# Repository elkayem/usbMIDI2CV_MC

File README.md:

# usbMIDI2CV_MC

This repository contains the code and schematics for a three-channel USB-MIDI to CV converter.  STL files are also included for a 3D printed case.  This project has the following features:
* Three channel Note CV output (88 keys, 1V/octave, MIDI channels 1-3) using a 12-bit DAC
* Configurable note priority for each channel (Top Note, Bottom Note, or Last Note Priority)
* Note scale factor calibration configurable in software
* 5V Gate/Trigger outputs, where each channel can be independently configured to either output a gate (output high for entire length of time that note is on) or trigger (20 msec pulse each time a new note is initiated)
* Velocity CV output (0 to 4V) for each channel
* Pitch Bend CV output (0.5 +/- 0.5V), which can be configured for channel 1, 2, or 3
* Control Change CV output (0 to 4V), which can be configured for channel 1, 2, or 3
* OLED user interface, used for setting parameters and saving to EEPROM

This module is the perfect interface between your computer or iPad and an analog synthesizer.  It can independently drive up to three oscillators with 1V/octave CV inputs.  (Connection to an iPad requires the USB camera adapter but is well worth it given the wide variety of great MIDI sequencer apps.)  

Note priority can be independengly set for each channel, with the following options:
* **Top Note (aka Highest Note):** When multiple notes are sounded simultaneously, the highest note being held will be sounded.  When the highest note is released, the next highest note will be played, and so on.
* **Bottom Note (aka Lowest Note):** Analagous to top note, except the lowest note being held will be sounded.  
* **Last Note:** The most recent note played will be sounded.  When that note is released, the next most recent note still being held will be sounded.  

The settings screen shows the current settings used.  Note priority is listed as sequence of three letters showing the setting for each of the three channels, where T = Top Note, B = Bottom Note, and L = Last Note.  Similarly, Gate/Trigger is listed as a sequence of three letters where G = Gate and T = Trigger.  Pitch Bend and CC settings show which MIDI channel will be used for the analog output.  Note scale factor can also be calibrated by +/-10%.  All of these settings can be set through the OLED interface using the encoder knob.

## Parts List
* Teensy 2.0
* LM7805 5V Voltage Regulator
* 128x64 OLED graphic display, with I2C interface 
* Pushbutton Rotary encoder with knob (should have 5 pins)
* 4x MCP4822 12-bit DACs (8 pin DIP)
* 2x LM324N Quad Op Amp (14 pin DIP)
* 7x 0.1 uF ceramic capacitors
* 0.33 uF capacitor
* 3x 3K resistors (1% metal film)
* 3x 4.7K resistors (1% metal film)
* 3x 10K resistors (1% metal film)
* 3x 2K resistors
* 4x 8 pin DIP IC sockets
* 2x 14 pin DIP IC sockets
* 2x 12-pin female headers
* 8x banana jacks
* 3x 1/4" mono phone jacks
* (Optional) 2-pin 5.08mm pitch screw terminal, for power input 
* Barrel power jack (e.g., 2.1 x 5.5 mm)
* 9 - 12V DC power supply with barrel connector (e.g., 2.1 x 5.5 mm)
* PCB (Gerber files included) or strip board
* 6x 10mm M3 bolts and nuts (4 for panel, 2 for USB port)
* 4x M2 bolts and nuts for mounting the OLED screen
* Panel mount USB 2.0 USB Mini B Female to USB Mini B Male, 1 ft cable (see picture below)

## Instructions
Electronic components can be soldered to a strip board or (more conveniently) to the PCB design I have included in this repository.  I recommend using IC sockets to mount the ICs and female headers to mount the Teensy.  The PCB can be manufactured by a PCB supplier.  The least expensive way to do this is to upload the gerber files (included as a .zip file) to one of several Chinese manufacturers such as SchenZhen2U, EasyEDA, or Seeed Studio.  pcbshopper.com allows a comparison between vendors.  Typical prices are $1-$3/board, with a minimum of 5 boards.  Recommended default settings are Layers: 2; PCB Thickness: 1.6mm; Surface Finish: HASL; Copper Weight: 1.  (Alternatively, contact me since I may still have a few extras I could send out for $5 + shipping.)

**Important!** Before connecting the Teensy 2.0 to an external power supply, the 5V pads must be cut on the bottom side of the board.  See https://www.pjrc.com/teensy/external_power.html for details.

The 3D printer STL files are located in the 3D Printer Files folder. I've also included the Sketchup file, in case modifications are needed.  (Download Sketchup Make, it's free!) The panel includes raised text, and so must be printed with two colors. Most slicers include a "pause at height" plugin, which will move the hot end out of the way and allow you to switch filaments. The panels are 3mm thick, and the letters are 0.45mm thick. I printed with 0.15mm layer thickness, allowing the letters to be printed in three layers. Add the command to pause after you finish printing the 3mm layer, so you can change the filament color. (One tip: If you find that your printer is disabling the stepper motors after pausing, you may need to insert M84 S0 at the start of the G-Code. I did.)  

The 3D printed panel must be printed with supports for the OLED screen mount. There is a recessed area on the back side of the panel that fits the screen mounting shape. I recommend picking up the screen by DIYMall, as the hole pattern was designed for that screen. Others may fit as well. Supports are not required for the case.

I have included 1/4" jacks for the CV note outputs to ensure that the analog synthesizer shares a common ground with the MIDI2CV component.  Ground is carried over the sleeve.  The sleeve pins on the phone jacks need to be tied together, and then tied to a ground location on the PCB.  I did not provide a dedicated ground location on the PCB for this connection, but any location on the PCB will work.  (e.g., directly to the power ground input).  I left the remainder of the outputs as banana jacks assuming at least one of the notes is connected.  If desired, the banana jacks can be replaced with phone jacks.  Be aware that the holes in the 3D printed case may need to be enlarged, and and the case may need to be made taller to accomodate the depth of the additional phone jacks. 

The rotary encoder should have three pins on one side and two on the other.  Connect the three pins to the 3 ENC headers on the board, and the two pins to the 2 BTN pins on the board.  These may be connected using jumper wires and male header pins, or soldered directly to the board.

The OLED attaches to the I2C output on the PCB (marked as 5V, GND, SCL, SDA).  Note the pin order!  This order matches a commonly available OLED from DIYMall, but other OLEDs exist with the power and ground swapped.  Swapping power and ground will destroy the OLED.

The firmware can be uploaded to the Teensy 2.0 using the Teensy loader.  See https://www.pjrc.com/teensy/first_use.html for details.  The hex file is included in this repository.  If modification of the source code is required, then the Arduino software and Teensyduino must also be installed (see https://www.pjrc.com/teensy/td_download.html).  Several libraries are used, which are included as part of the Teensyduino installer.  Be sure to configure the board as Teensy 2.0 (under Tools > Board), and USB Port as MIDI (under Tools > USB Type).

**Important Notes if recompiling firmware:**  
* You must be using Teensyduino 1.45 or later to recompile the software.  Earlier versions used a different internal numbering convention for MIDI message types.  The latest version can be downloaded from https://www.pjrc.com/teensy/td_download.html.  
* If the software isn't compiling, check your library version numbers.  I am currently using Adafruit SSD1306 v1.2.9 and Bounce2 v2.52.2.  The remaining libraries should come preinstalled with the Arduino and Teensyduino installers.

If using 1% metal film resistors, the MIDI2CV is likely to be in tune for the entire 7.25 octave (88 key) range.  The DAC output range is 4.096 V, which is amplified by 7.25/4.096 = 1.7700.  This is accomplished with the combination of 3K, 4.7K, and 10K resistors in the op-amp circuit.  (Note 3.01K is also common, and can be used.)  

If the MIDI2CV output scale factor isn't exactly 1V/octave, the scale factor can be adjusted by +/-10% using the user interface.  Mine was fairly close for all three channels, and required adjustment of only a few tenths of a percent.

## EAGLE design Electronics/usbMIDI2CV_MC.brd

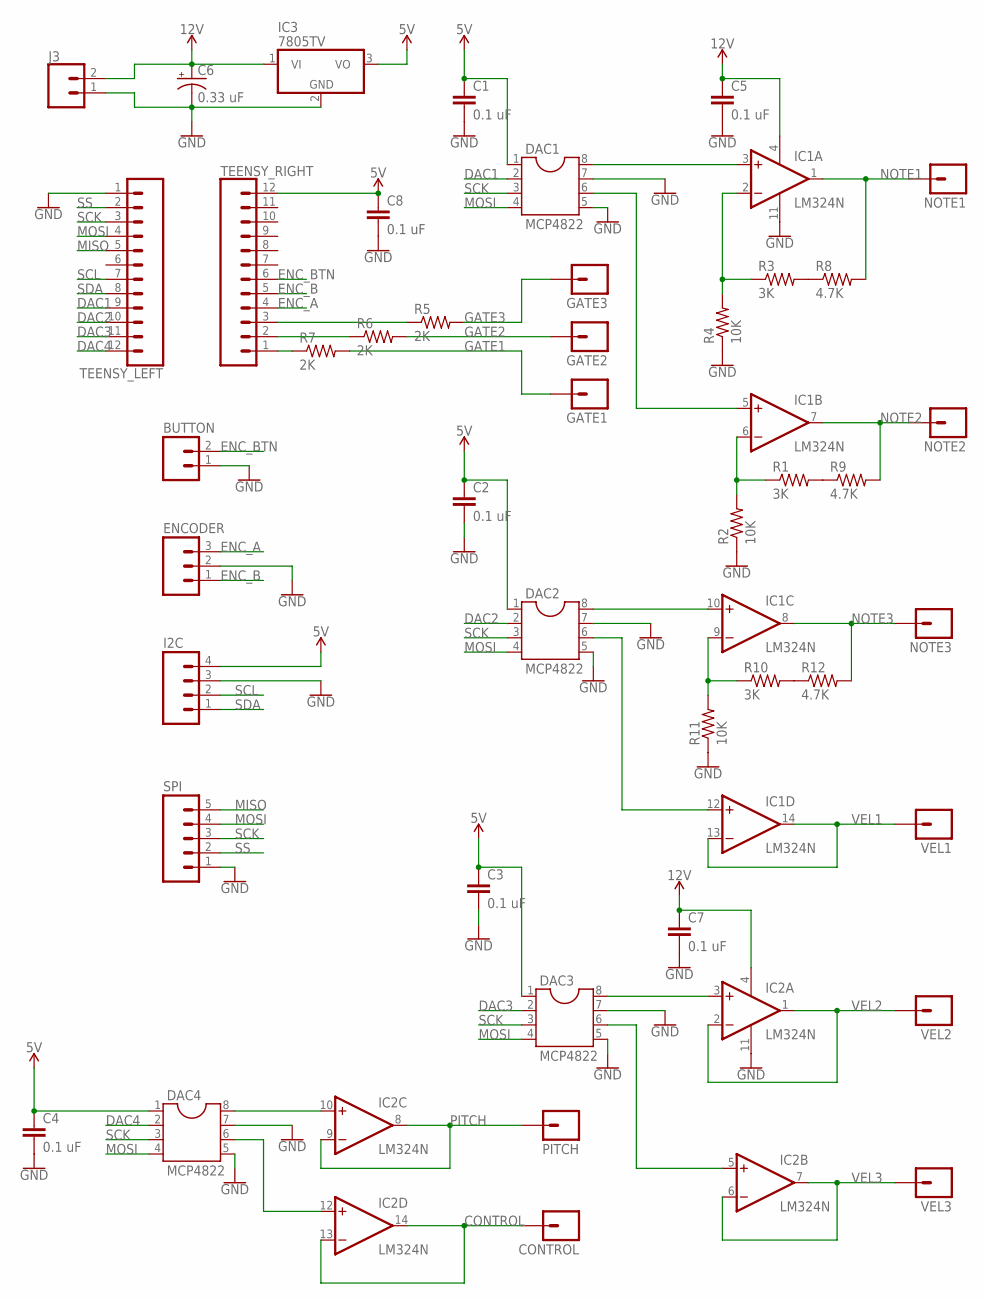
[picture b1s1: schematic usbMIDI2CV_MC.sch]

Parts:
BUTTON: M02LOCK_LONGPADS; 1X02_LOCK_LONGPADS
C1, C2, C3, C4, C5, C7, C8: 0.1 uF; CAP-PTH-SMALL
C6: 0.33 uF; CPOL-RADIAL-100UF-25V
CONTROL: M01PTH_NO_SILK_YES_STOP; 1X01_NO_SILK
DAC1, DAC2, DAC3, DAC4: MCP4822; SOCKET-08
ENCODER: M03LONGPADS; 1X03_LONGPADS
GATE1, GATE2, GATE3: M01PTH_NO_SILK_YES_STOP; 1X01_NO_SILK
I2C: M04LONGPADS; 1X04_LONGPADS
IC1, IC2: LM324N; DIL14
IC3: 7805TV; TO220V
J3: CONN_025MM; SCREWTERMINAL-5MM-2
NOTE1, NOTE2, NOTE3: M01PTH_NO_SILK_YES_STOP; 1X01_NO_SILK
PITCH: M01PTH_NO_SILK_YES_STOP; 1X01_NO_SILK
R1, R3, R10: 3K; 0207/10
R2, R4, R11: 10K; 0207/10
R5, R6, R7: 2K; 0207/10
R8, R9, R12: 4.7K; 0207/10
SPI: M05PTH_LONGPADS; 1X05_LONGPADS
TEENSY_LEFT: CONN_12; 1X12
TEENSY_RIGHT: CONN_12; 1X12
VEL1, VEL2, VEL3: M01PTH_NO_SILK_YES_STOP; 1X01_NO_SILK

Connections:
5V: C1.1, C2.1, C3.1, C4.1, C8.1, DAC1.1, DAC2.1, DAC3.1, DAC4.1, I2C.4, IC3.3 (VO), TEENSY_RIGHT.12
12V: C5.1, C6.1 (+), C7.1, IC1.4 (V+), IC2.4 (V+), IC3.1 (VI), J3.2
CONTROL: CONTROL.1, IC2.13 (-IN), IC2.14 (OUT)
DAC1: DAC1.2, TEENSY_LEFT.9
DAC2: DAC2.2, TEENSY_LEFT.10
DAC3: DAC3.2, TEENSY_LEFT.11
DAC4: DAC4.2, TEENSY_LEFT.12
ENC_A: ENCODER.3, TEENSY_RIGHT.4
ENC_B: ENCODER.1, TEENSY_RIGHT.5
ENC_BTN: BUTTON.2, TEENSY_RIGHT.6
GATE1: GATE1.1, R7.2
GATE2: GATE2.1, R6.2
GATE3: GATE3.1, R5.2
GND: BUTTON.1, C1.2, C2.2, C3.2, C4.2, C5.2, C6.2 (-), C7.2, C8.2, DAC1.5, DAC1.7, DAC2.5, DAC2.7, DAC3.5, DAC3.7, DAC4.5, DAC4.7, ENCODER.2, I2C.3, IC1.11 (V-), IC2.11 (V-), IC3.2 (GND), J3.1, R2.1, R4.1, R11.1, SPI.1, TEENSY_LEFT.1
MISO: SPI.5, TEENSY_LEFT.5
MOSI: DAC1.4, DAC2.4, DAC3.4, DAC4.4, SPI.4, TEENSY_LEFT.4
unnamed: IC1.6 (-IN), R1.1, R2.2
unnamed: R1.2, R9.1
unnamed: IC1.9 (-IN), R10.1, R11.2
unnamed: DAC1.8, IC1.3 (+IN)
unnamed: R3.2, R8.1
unnamed: IC1.2 (-IN), R3.1, R4.2
unnamed: DAC1.6, IC1.5 (+IN)
unnamed: DAC2.8, IC1.10 (+IN)
unnamed: DAC2.6, IC1.12 (+IN)
unnamed: R10.2, R12.1
unnamed: DAC3.8, IC2.3 (+IN)
unnamed: R5.1, TEENSY_RIGHT.3
unnamed: DAC3.6, IC2.5 (+IN)
unnamed: DAC4.6, IC2.12 (+IN)
unnamed: DAC4.8, IC2.10 (+IN)
unnamed: R6.1, TEENSY_RIGHT.2
unnamed: R7.1, TEENSY_RIGHT.1
NOTE1: IC1.1 (OUT), NOTE1.1, R8.2
NOTE2: IC1.7 (OUT), NOTE2.1, R9.2
NOTE3: IC1.8 (OUT), NOTE3.1, R12.2
PITCH: IC2.8 (OUT), IC2.9 (-IN), PITCH.1
SCK: DAC1.3, DAC2.3, DAC3.3, DAC4.3, SPI.3, TEENSY_LEFT.3
SCL: I2C.2, TEENSY_LEFT.7
SDA: I2C.1, TEENSY_LEFT.8
SS: SPI.2, TEENSY_LEFT.2
VEL1: IC1.13 (-IN), IC1.14 (OUT), VEL1.1
VEL2: IC2.1 (OUT), IC2.2 (-IN), VEL2.1
VEL3: IC2.6 (-IN), IC2.7 (OUT), VEL3.1

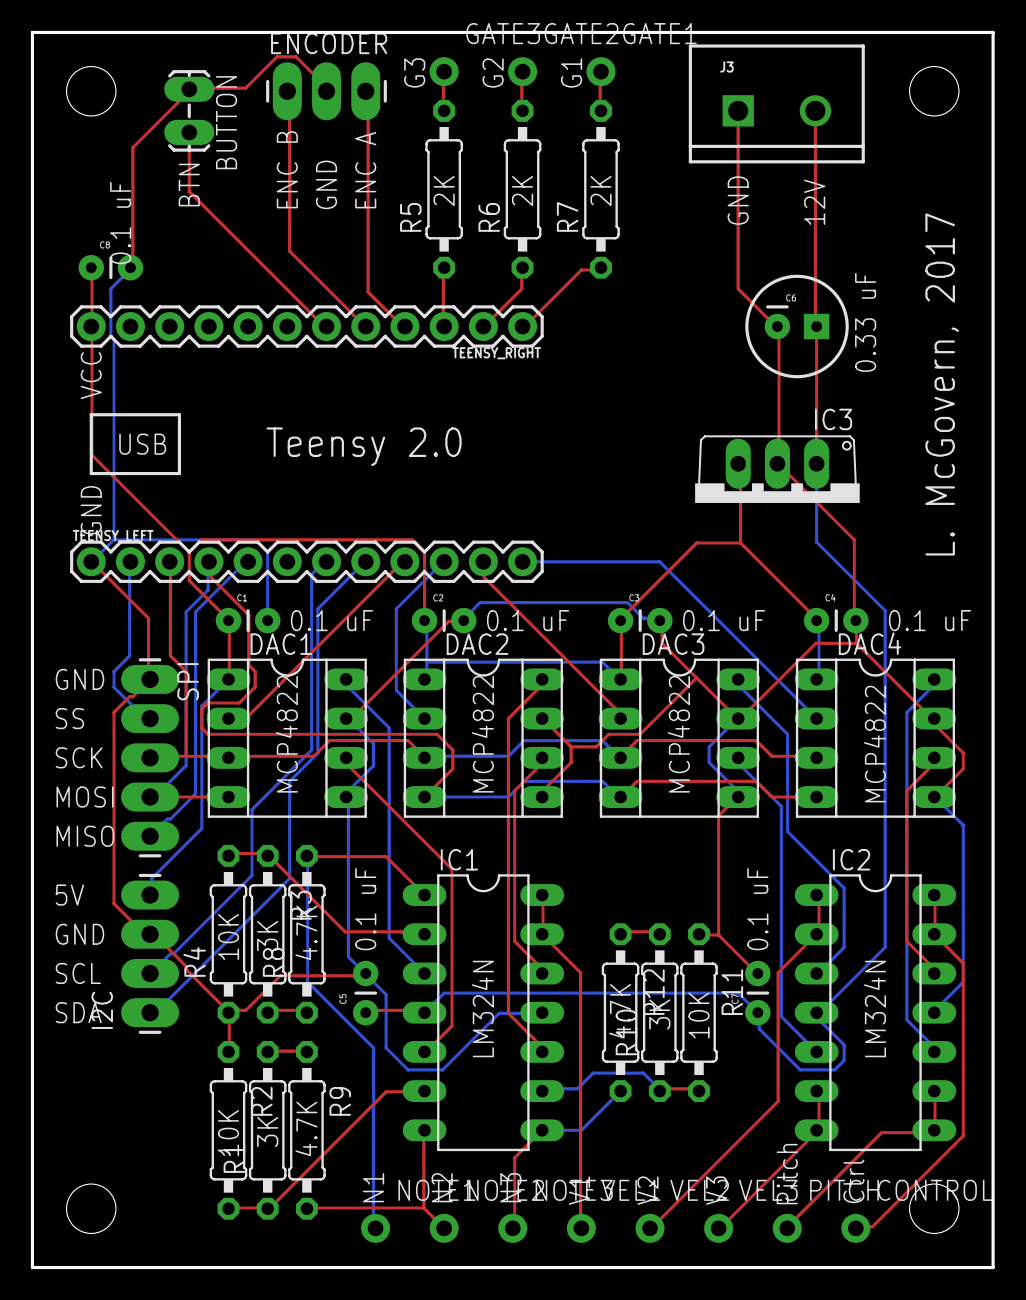
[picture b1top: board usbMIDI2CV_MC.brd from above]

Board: 2 copper layers, 62.2 x 80.0 mm, 45 parts (0 on the bottom side), 44 nets.

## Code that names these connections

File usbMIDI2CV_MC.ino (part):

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#define GATE_CH1  12
#define GATE_CH2  13

#define ENC_A   14
#define ENC_B   15
#define ENC_BTN 16


#define GATE(CH) (CH==0 ? GATE_CH0 : (CH==1 ? GATE_CH1 : GATE_CH2))
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 pinMode(DAC2, OUTPUT);
 pinMode(DAC3, OUTPUT);
 pinMode(DAC4, OUTPUT);
 pinMode(ENC_A, INPUT_PULLUP);
 pinMode(ENC_B, INPUT_PULLUP);
 pinMode(ENC_BTN,INPUT_PULLUP);
  
 digitalWrite(GATE_CH0,LOW);
 digitalWrite(GATE_CH1,LOW);
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}

// setVoltage -- Set DAC voltage output
// dacpin: chip select pin for DAC.  Note and velocity on DAC1, pitch bend and CC on DAC2
// channel: 0 (A) or 1 (B).  
// gain: 0 = 1X, 1 = 2X.  
// mV: integer 0 to 4095.  If gain is 1X, mV is in units of half mV (i.e., 0 to 2048 mV).
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
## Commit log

2017-12-28 Initial check-in
2018-01-06 Add note scale factor calibration support.
2018-01-06 update photo
2018-05-26 Add board pdf
2018-06-30 Update for compatibility with Teensyduino 1.41 and later.
2019-01-23 Update OLED library and hex file

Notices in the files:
usbMIDI2CV_MC.ino:
Copyright (C) 2018  Larry McGovern
This program is free software: you can redistribute it and/or modify
it under the terms of the GNU General Public License as published by
the Free Software Foundation, either version 3 of the License, or
(at your option) any later version.
parts and their libraries:
SparkFun-Connectors: Licensing: Creative Commons ShareAlike 4.0 International - https://creativecommons.org/licenses/by-sa/4.0
